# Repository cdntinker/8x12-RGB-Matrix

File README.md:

This silly little RGB matrix board is specifically designed to be glued to the back of a standard North American single gang blank wallplate & fit inside the opening of a WireMold surface mount box.

> [!TIP]
> It is distinctly possible that not ALL of tthe decoupling capacitors(C1-C96) are actually required.
> (Tho it is certain that some of them are...)

> [!CAUTION]
> This board currently has no reverse-polarity protection.
> 
> It also now has footprints for an optional 800uf of bulk capacitance in the form of tantalum capacitors.
> 
> Reverse-polarity power will not only fry the poor LEDs, it'll potentially cause **BOOM** noises.

> [!NOTE]
> This is a bit of a power hungry beast.
> The SK6812mini is rated at up to 0.2W & there are 96 of them here. That's 19.2W overall...
> There is a good possibility that you'll need something significantly more than the typical USB charger to power it.

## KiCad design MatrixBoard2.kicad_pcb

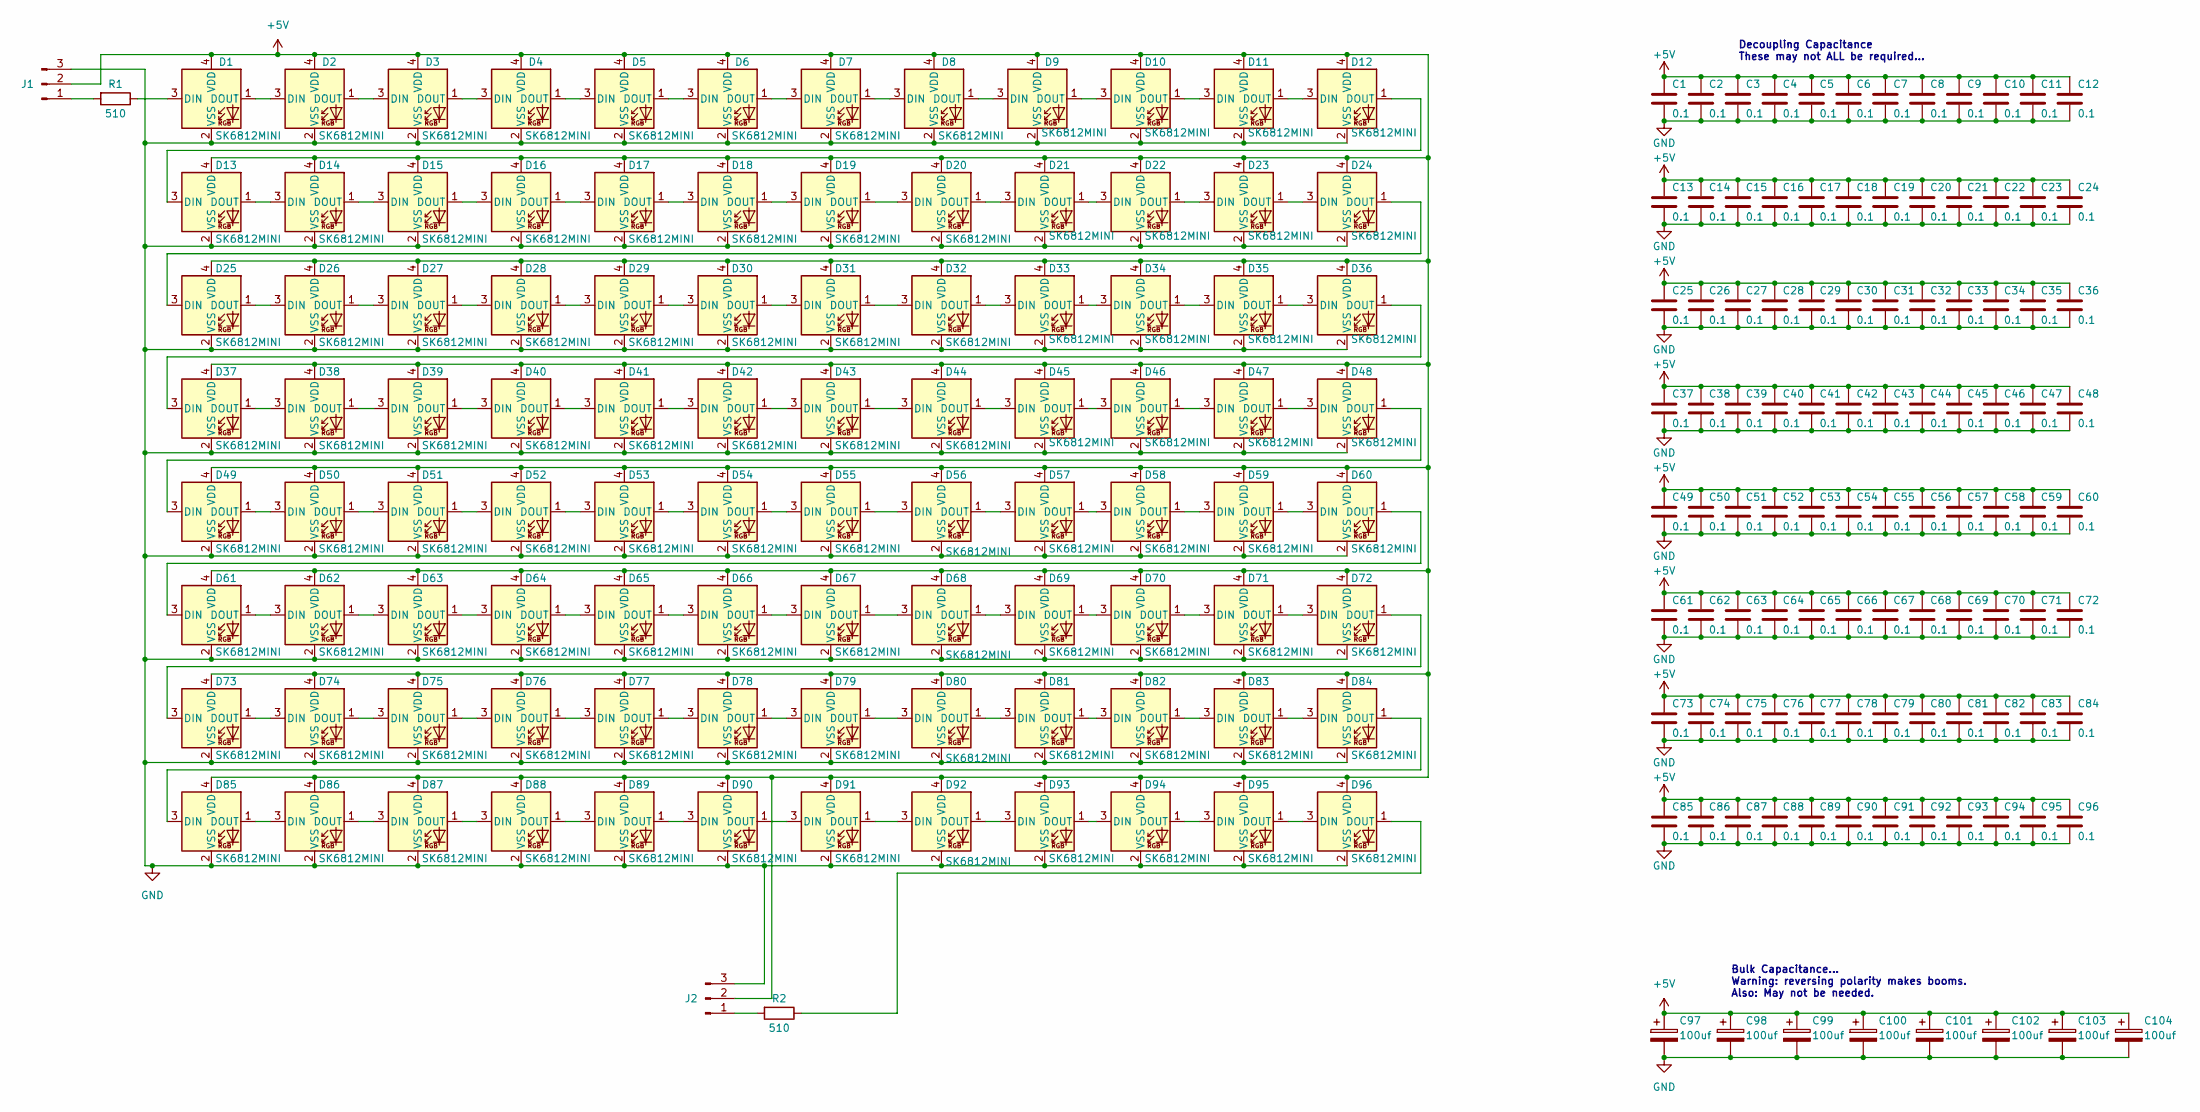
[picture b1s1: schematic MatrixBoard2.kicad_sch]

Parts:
C1, C2, C3, C4, C5, C6, C7, C8, C9, C10, C11, C12, C13, C14, C15, C16, C17, C18, C19, C20, C21, C22, C23, C24, C25, C26, C27, C28, C29, C30, C31, C32, C33, C34, C35, C36, C37, C38, C39, C40, C41, C42, C43, C44, C45, C46, C47, C48, C49, C50, C51, C52, C53, C54, C55, C56, C57, C58, C59, C60, C61, C62, C63, C64, C65, C66, C67, C68, C69, C70, C71, C72, C73, C74, C75, C76, C77, C78, C79, C80, C81, C82, C83, C84, C85, C86, C87, C88, C89, C90, C91, C92, C93, C94, C95, C96: 0.1; C_0603_1608Metric
C97, C98, C99, C100, C101, C102, C103, C104: 100uf; CP_EIA-6032-28_Kemet-C_Pad2.25x2.35mm_HandSolder
D1, D2, D3, D4, D5, D6, D7, D8, D9, D10, D11, D12, D13, D14, D15, D16, D17, D18, D19, D20, D21, D22, D23, D24, D25, D26, D27, D28, D29, D30, D31, D32, D33, D34, D35, D36, D37, D38, D39, D40, D41, D42, D43, D44, D45, D46, D47, D48, D49, D50, D51, D52, D53, D54, D55, D56, D57, D58, D59, D60, D61, D62, D63, D64, D65, D66, D67, D68, D69, D70, D71, D72, D73, D74, D75, D76, D77, D78, D79, D80, D81, D82, D83, D84, D85, D86, D87, D88, D89, D90, D91, D92, D93, D94, D95, D96: SK6812MINI; LED_SK6812MINI_PLCC4_3.5x3.5mm_P1.75mm
J1, J2: Conn_01x03_Male; PinHeader_1x03_P2.54mm_Vertical
R1, R2: 510; R_0805_2012Metric

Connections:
+5V: C1.1, C2.1, C3.1, C4.1, C5.1, C6.1, C7.1, C8.1, C9.1, C10.1, C11.1, C12.1, C13.1, C14.1, C15.1, C16.1, C17.1, C18.1, C19.1, C20.1, C21.1, C22.1, C23.1, C24.1, C25.1, C26.1, C27.1, C28.1, C29.1, C30.1, C31.1, C32.1, C33.1, C34.1, C35.1, C36.1, C37.1, C38.1, C39.1, C40.1, C41.1, C42.1, C43.1, C44.1, C45.1, C46.1, C47.1, C48.1, C49.1, C50.1, C51.1, C52.1, C53.1, C54.1, C55.1, C56.1, C57.1, C58.1, C59.1, C60.1, C61.1, C62.1, C63.1, C64.1, C65.1, C66.1, C67.1, C68.1, C69.1, C70.1, C71.1, C72.1, C73.1, C74.1, C75.1, C76.1, C77.1, C78.1, C79.1, C80.1, C81.1, C82.1, C83.1, C84.1, C85.1, C86.1, C87.1, C88.1, C89.1, C90.1, C91.1, C92.1, C93.1, C94.1, C95.1, C96.1, C97.1, C98.1, C99.1, C100.1, C101.1, C102.1, C103.1, C104.1, D1.4 (VDD), D2.4 (VDD), D3.4 (VDD), D4.4 (VDD), D5.4 (VDD), D6.4 (VDD), D7.4 (VDD), D8.4 (VDD), D9.4 (VDD), D10.4 (VDD), D11.4 (VDD), D12.4 (VDD), D13.4 (VDD), D14.4 (VDD), D15.4 (VDD), D16.4 (VDD), D17.4 (VDD), D18.4 (VDD), D19.4 (VDD), D20.4 (VDD), D21.4 (VDD), D22.4 (VDD), D23.4 (VDD), D24.4 (VDD), D25.4 (VDD), D26.4 (VDD), D27.4 (VDD), D28.4 (VDD), D29.4 (VDD), D30.4 (VDD), D31.4 (VDD), D32.4 (VDD), D33.4 (VDD), D34.4 (VDD), D35.4 (VDD), D36.4 (VDD), D37.4 (VDD), D38.4 (VDD), D39.4 (VDD), D40.4 (VDD), D41.4 (VDD), D42.4 (VDD), D43.4 (VDD), D44.4 (VDD), D45.4 (VDD), D46.4 (VDD), D47.4 (VDD), D48.4 (VDD), D49.4 (VDD), D50.4 (VDD), D51.4 (VDD), D52.4 (VDD), D53.4 (VDD), D54.4 (VDD), D55.4 (VDD), D56.4 (VDD), D57.4 (VDD), D58.4 (VDD), D59.4 (VDD), D60.4 (VDD), D61.4 (VDD), D62.4 (VDD), D63.4 (VDD), D64.4 (VDD), D65.4 (VDD), D66.4 (VDD), D67.4 (VDD), D68.4 (VDD), D69.4 (VDD), D70.4 (VDD), D71.4 (VDD), D72.4 (VDD), D73.4 (VDD), D74.4 (VDD), D75.4 (VDD), D76.4 (VDD), D77.4 (VDD), D78.4 (VDD), D79.4 (VDD), D80.4 (VDD), D81.4 (VDD), D82.4 (VDD), D83.4 (VDD), D84.4 (VDD), D85.4 (VDD), D86.4 (VDD), D87.4 (VDD), D88.4 (VDD), D89.4 (VDD), D90.4 (VDD), D91.4 (VDD), D92.4 (VDD), D93.4 (VDD), D94.4 (VDD), D95.4 (VDD), D96.4 (VDD), J1.2, J2.2
GND: C1.2, C2.2, C3.2, C4.2, C5.2, C6.2, C7.2, C8.2, C9.2, C10.2, C11.2, C12.2, C13.2, C14.2, C15.2, C16.2, C17.2, C18.2, C19.2, C20.2, C21.2, C22.2, C23.2, C24.2, C25.2, C26.2, C27.2, C28.2, C29.2, C30.2, C31.2, C32.2, C33.2, C34.2, C35.2, C36.2, C37.2, C38.2, C39.2, C40.2, C41.2, C42.2, C43.2, C44.2, C45.2, C46.2, C47.2, C48.2, C49.2, C50.2, C51.2, C52.2, C53.2, C54.2, C55.2, C56.2, C57.2, C58.2, C59.2, C60.2, C61.2, C62.2, C63.2, C64.2, C65.2, C66.2, C67.2, C68.2, C69.2, C70.2, C71.2, C72.2, C73.2, C74.2, C75.2, C76.2, C77.2, C78.2, C79.2, C80.2, C81.2, C82.2, C83.2, C84.2, C85.2, C86.2, C87.2, C88.2, C89.2, C90.2, C91.2, C92.2, C93.2, C94.2, C95.2, C96.2, C97.2, C98.2, C99.2, C100.2, C101.2, C102.2, C103.2, C104.2, D1.2 (VSS), D2.2 (VSS), D3.2 (VSS), D4.2 (VSS), D5.2 (VSS), D6.2 (VSS), D7.2 (VSS), D8.2 (VSS), D9.2 (VSS), D10.2 (VSS), D11.2 (VSS), D12.2 (VSS), D13.2 (VSS), D14.2 (VSS), D15.2 (VSS), D16.2 (VSS), D17.2 (VSS), D18.2 (VSS), D19.2 (VSS), D20.2 (VSS), D21.2 (VSS), D22.2 (VSS), D23.2 (VSS), D24.2 (VSS), D25.2 (VSS), D26.2 (VSS), D27.2 (VSS), D28.2 (VSS), D29.2 (VSS), D30.2 (VSS), D31.2 (VSS), D32.2 (VSS), D33.2 (VSS), D34.2 (VSS), D35.2 (VSS), D36.2 (VSS), D37.2 (VSS), D38.2 (VSS), D39.2 (VSS), D40.2 (VSS), D41.2 (VSS), D42.2 (VSS), D43.2 (VSS), D44.2 (VSS), D45.2 (VSS), D46.2 (VSS), D47.2 (VSS), D48.2 (VSS), D49.2 (VSS), D50.2 (VSS), D51.2 (VSS), D52.2 (VSS), D53.2 (VSS), D54.2 (VSS), D55.2 (VSS), D56.2 (VSS), D57.2 (VSS), D58.2 (VSS), D59.2 (VSS), D60.2 (VSS), D61.2 (VSS), D62.2 (VSS), D63.2 (VSS), D64.2 (VSS), D65.2 (VSS), D66.2 (VSS), D67.2 (VSS), D68.2 (VSS), D69.2 (VSS), D70.2 (VSS), D71.2 (VSS), D72.2 (VSS), D73.2 (VSS), D74.2 (VSS), D75.2 (VSS), D76.2 (VSS), D77.2 (VSS), D78.2 (VSS), D79.2 (VSS), D80.2 (VSS), D81.2 (VSS), D82.2 (VSS), D83.2 (VSS), D84.2 (VSS), D85.2 (VSS), D86.2 (VSS), D87.2 (VSS), D88.2 (VSS), D89.2 (VSS), D90.2 (VSS), D91.2 (VSS), D92.2 (VSS), D93.2 (VSS), D94.2 (VSS), D95.2 (VSS), D96.2 (VSS), J1.3, J2.3
unnamed: D1.1 (DOUT), D2.3 (DIN)
unnamed: D1.3 (DIN), R1.1
unnamed: D2.1 (DOUT), D3.3 (DIN)
unnamed: D3.1 (DOUT), D4.3 (DIN)
unnamed: D4.1 (DOUT), D5.3 (DIN)
unnamed: D5.1 (DOUT), D6.3 (DIN)
unnamed: D6.1 (DOUT), D7.3 (DIN)
unnamed: D7.1 (DOUT), D8.3 (DIN)
unnamed: D8.1 (DOUT), D9.3 (DIN)
unnamed: D10.1 (DOUT), D11.3 (DIN)
unnamed: D9.1 (DOUT), D10.3 (DIN)
unnamed: D11.1 (DOUT), D12.3 (DIN)
unnamed: D12.1 (DOUT), D13.3 (DIN)
unnamed: D13.1 (DOUT), D14.3 (DIN)
unnamed: D14.1 (DOUT), D15.3 (DIN)
unnamed: D15.1 (DOUT), D16.3 (DIN)
unnamed: D16.1 (DOUT), D17.3 (DIN)
unnamed: D17.1 (DOUT), D18.3 (DIN)
unnamed: D18.1 (DOUT), D19.3 (DIN)
unnamed: D19.1 (DOUT), D20.3 (DIN)
unnamed: D20.1 (DOUT), D21.3 (DIN)
unnamed: D21.1 (DOUT), D22.3 (DIN)
unnamed: D22.1 (DOUT), D23.3 (DIN)
unnamed: D23.1 (DOUT), D24.3 (DIN)
unnamed: D24.1 (DOUT), D25.3 (DIN)
unnamed: D25.1 (DOUT), D26.3 (DIN)
unnamed: D26.1 (DOUT), D27.3 (DIN)
unnamed: D27.1 (DOUT), D28.3 (DIN)
unnamed: D28.1 (DOUT), D29.3 (DIN)
unnamed: D29.1 (DOUT), D30.3 (DIN)
unnamed: D30.1 (DOUT), D31.3 (DIN)
unnamed: D31.1 (DOUT), D32.3 (DIN)
unnamed: D32.1 (DOUT), D33.3 (DIN)
unnamed: D33.1 (DOUT), D34.3 (DIN)
unnamed: D34.1 (DOUT), D35.3 (DIN)
unnamed: D35.1 (DOUT), D36.3 (DIN)
unnamed: D36.1 (DOUT), D37.3 (DIN)
unnamed: D37.1 (DOUT), D38.3 (DIN)
unnamed: D38.1 (DOUT), D39.3 (DIN)
unnamed: D39.1 (DOUT), D40.3 (DIN)
unnamed: D40.1 (DOUT), D41.3 (DIN)
unnamed: D41.1 (DOUT), D42.3 (DIN)
unnamed: D42.1 (DOUT), D43.3 (DIN)
unnamed: D43.1 (DOUT), D44.3 (DIN)
unnamed: D44.1 (DOUT), D45.3 (DIN)
unnamed: D45.1 (DOUT), D46.3 (DIN)
unnamed: D46.1 (DOUT), D47.3 (DIN)
unnamed: D47.1 (DOUT), D48.3 (DIN)
unnamed: D48.1 (DOUT), D49.3 (DIN)
unnamed: D49.1 (DOUT), D50.3 (DIN)
unnamed: D50.1 (DOUT), D51.3 (DIN)
unnamed: D51.1 (DOUT), D52.3 (DIN)
unnamed: D52.1 (DOUT), D53.3 (DIN)
unnamed: D53.1 (DOUT), D54.3 (DIN)
unnamed: D54.1 (DOUT), D55.3 (DIN)
unnamed: D55.1 (DOUT), D56.3 (DIN)
unnamed: D56.1 (DOUT), D57.3 (DIN)
unnamed: D57.1 (DOUT), D58.3 (DIN)
unnamed: D58.1 (DOUT), D59.3 (DIN)
unnamed: D59.1 (DOUT), D60.3 (DIN)
unnamed: D60.1 (DOUT), D61.3 (DIN)
unnamed: D61.1 (DOUT), D62.3 (DIN)
unnamed: D62.1 (DOUT), D63.3 (DIN)
unnamed: D63.1 (DOUT), D64.3 (DIN)
unnamed: D64.1 (DOUT), D65.3 (DIN)
unnamed: D65.1 (DOUT), D66.3 (DIN)
unnamed: D66.1 (DOUT), D67.3 (DIN)
unnamed: D67.1 (DOUT), D68.3 (DIN)
unnamed: D68.1 (DOUT), D69.3 (DIN)
unnamed: D69.1 (DOUT), D70.3 (DIN)
unnamed: D70.1 (DOUT), D71.3 (DIN)
unnamed: D71.1 (DOUT), D72.3 (DIN)
unnamed: D72.1 (DOUT), D73.3 (DIN)
unnamed: D73.1 (DOUT), D74.3 (DIN)
unnamed: D74.1 (DOUT), D75.3 (DIN)
unnamed: D75.1 (DOUT), D76.3 (DIN)
unnamed: D76.1 (DOUT), D77.3 (DIN)
unnamed: D77.1 (DOUT), D78.3 (DIN)
unnamed: D78.1 (DOUT), D79.3 (DIN)
unnamed: D79.1 (DOUT), D80.3 (DIN)
unnamed: D80.1 (DOUT), D81.3 (DIN)
unnamed: D81.1 (DOUT), D82.3 (DIN)
unnamed: D82.1 (DOUT), D83.3 (DIN)
unnamed: D83.1 (DOUT), D84.3 (DIN)
unnamed: D84.1 (DOUT), D85.3 (DIN)
unnamed: D85.1 (DOUT), D86.3 (DIN)
unnamed: D86.1 (DOUT), D87.3 (DIN)
unnamed: D87.1 (DOUT), D88.3 (DIN)
unnamed: D88.1 (DOUT), D89.3 (DIN)
unnamed: D89.1 (DOUT), D90.3 (DIN)
unnamed: D90.1 (DOUT), D91.3 (DIN)
unnamed: D91.1 (DOUT), D92.3 (DIN)
unnamed: D92.1 (DOUT), D93.3 (DIN)
unnamed: D93.1 (DOUT), D94.3 (DIN)
unnamed: D94.1 (DOUT), D95.3 (DIN)
unnamed: D95.1 (DOUT), D96.3 (DIN)
unnamed: D96.1 (DOUT), R2.1
unnamed: J1.1, R1.2
unnamed: J2.1, R2.2

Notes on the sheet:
Bulk Capacitance... Warning: reversing polarity makes booms. Also: May not be needed.
Decoupling Capacitance These may not ALL be required...

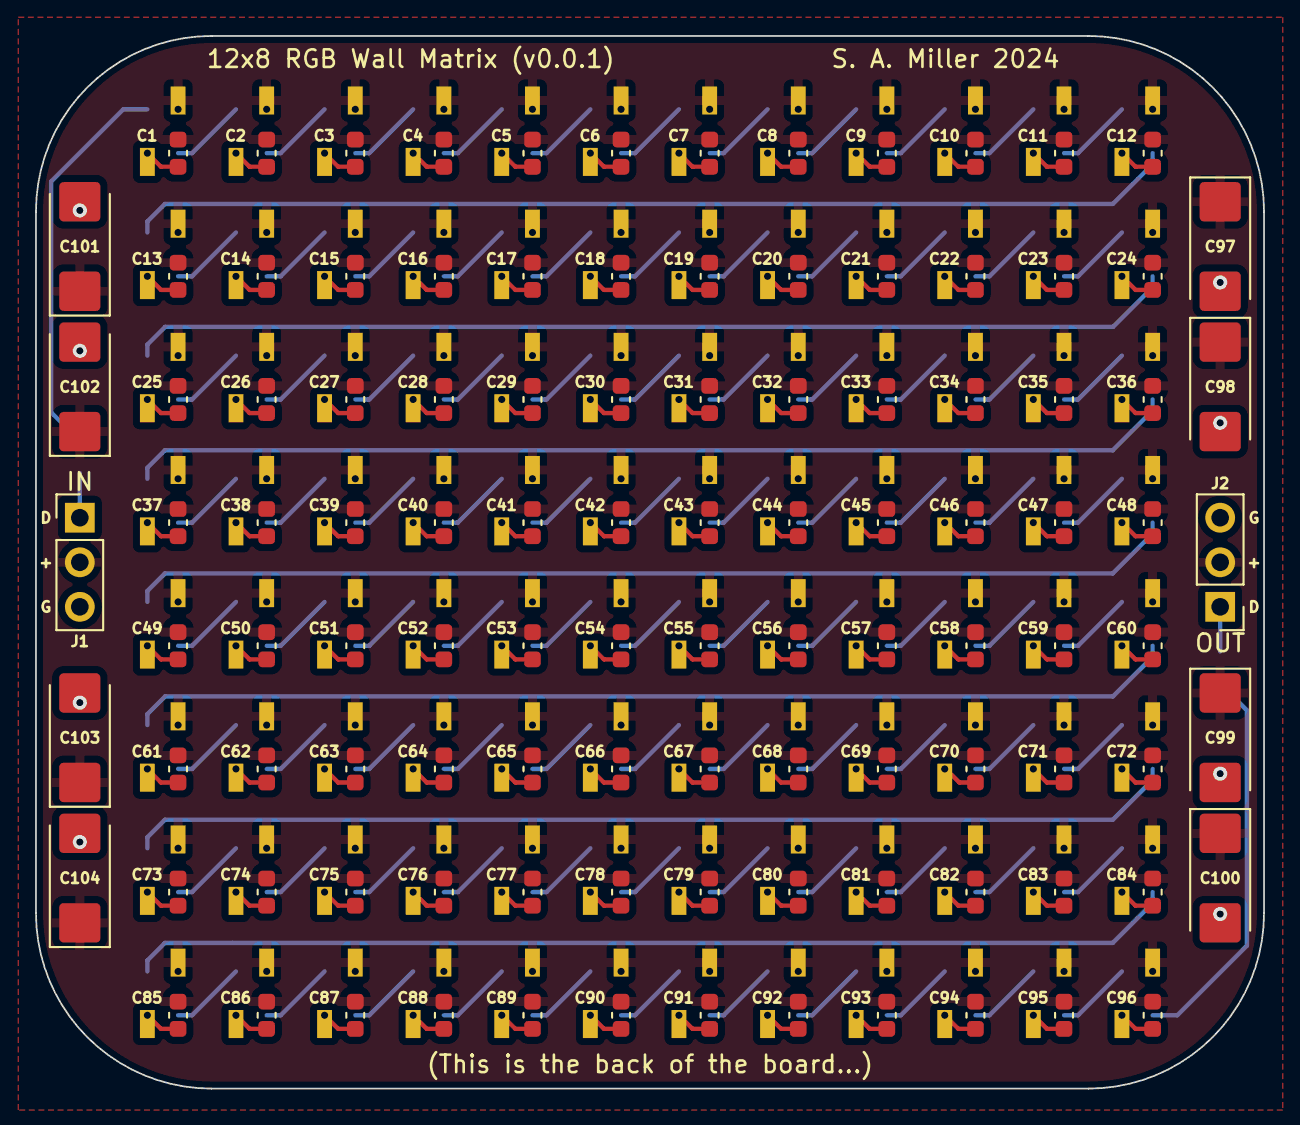
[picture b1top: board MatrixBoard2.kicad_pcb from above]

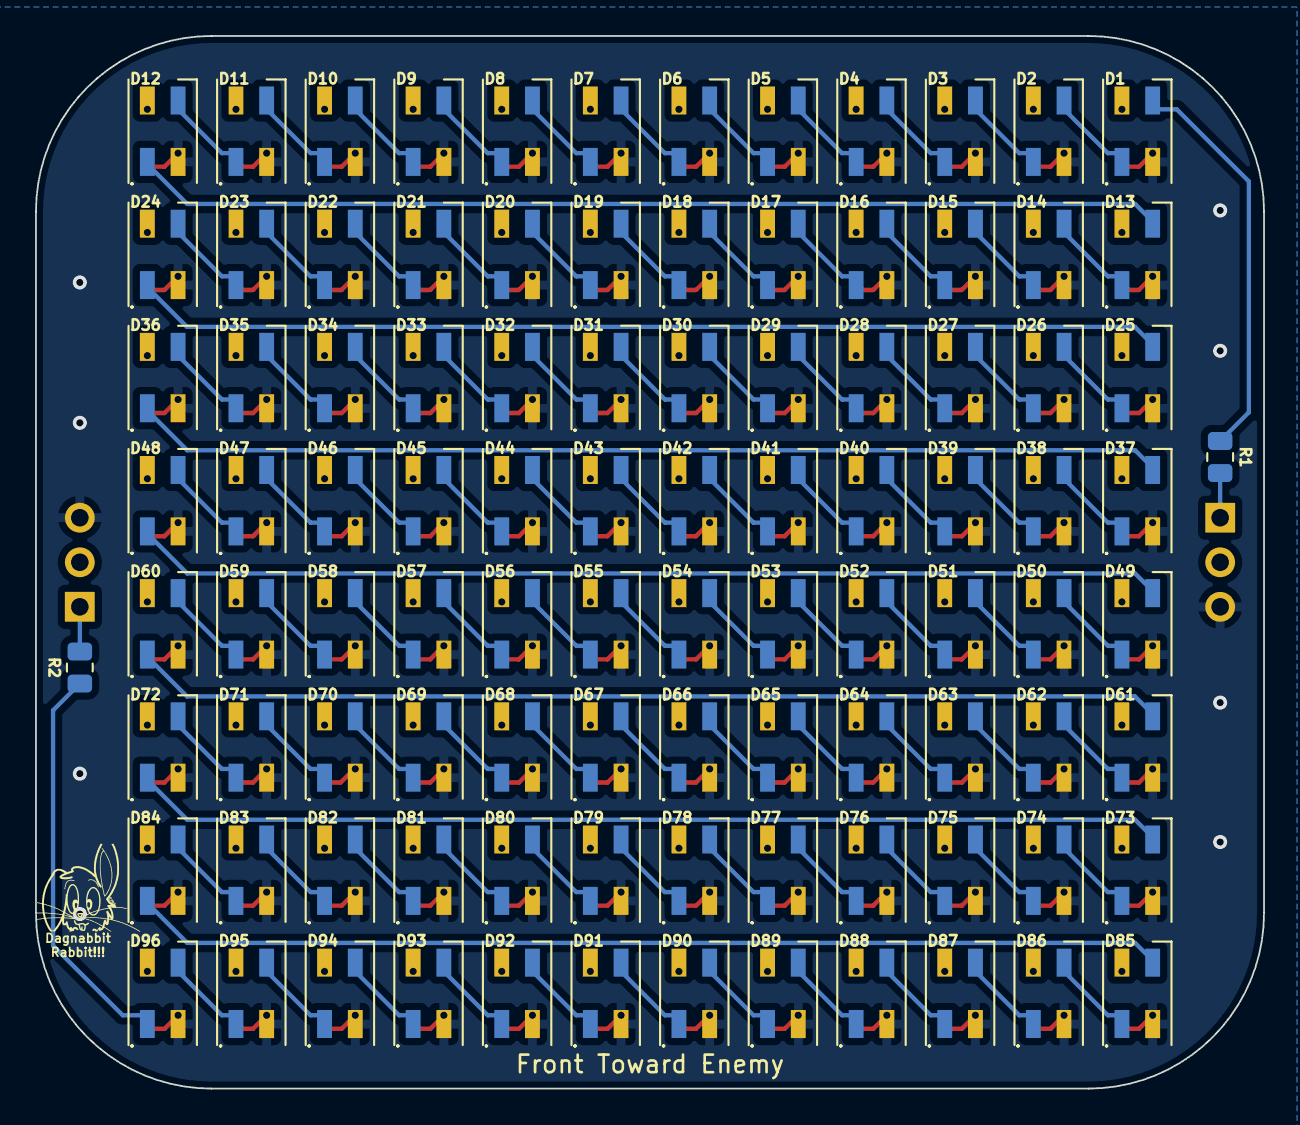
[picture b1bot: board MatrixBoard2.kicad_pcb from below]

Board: 2 copper layers, 70.0 x 60.0 mm, 204 parts (98 on the bottom side), 101 nets.

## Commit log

2024-01-16 fixing footprints
2024-01-16 Added datasheet for SK6812mini...
2024-01-17 Added possible Bulk Capacitance...
2024-01-17 Now with MOAR 3D
2024-01-17 A bunch of cosmetic changes... (Mostly silkscreen OCD)
2024-01-17 Added the rabbit back in...
2024-02-08 Did a bit o research into SK6812mini versions...
2024-03-09 bye bye bloody wrl files
